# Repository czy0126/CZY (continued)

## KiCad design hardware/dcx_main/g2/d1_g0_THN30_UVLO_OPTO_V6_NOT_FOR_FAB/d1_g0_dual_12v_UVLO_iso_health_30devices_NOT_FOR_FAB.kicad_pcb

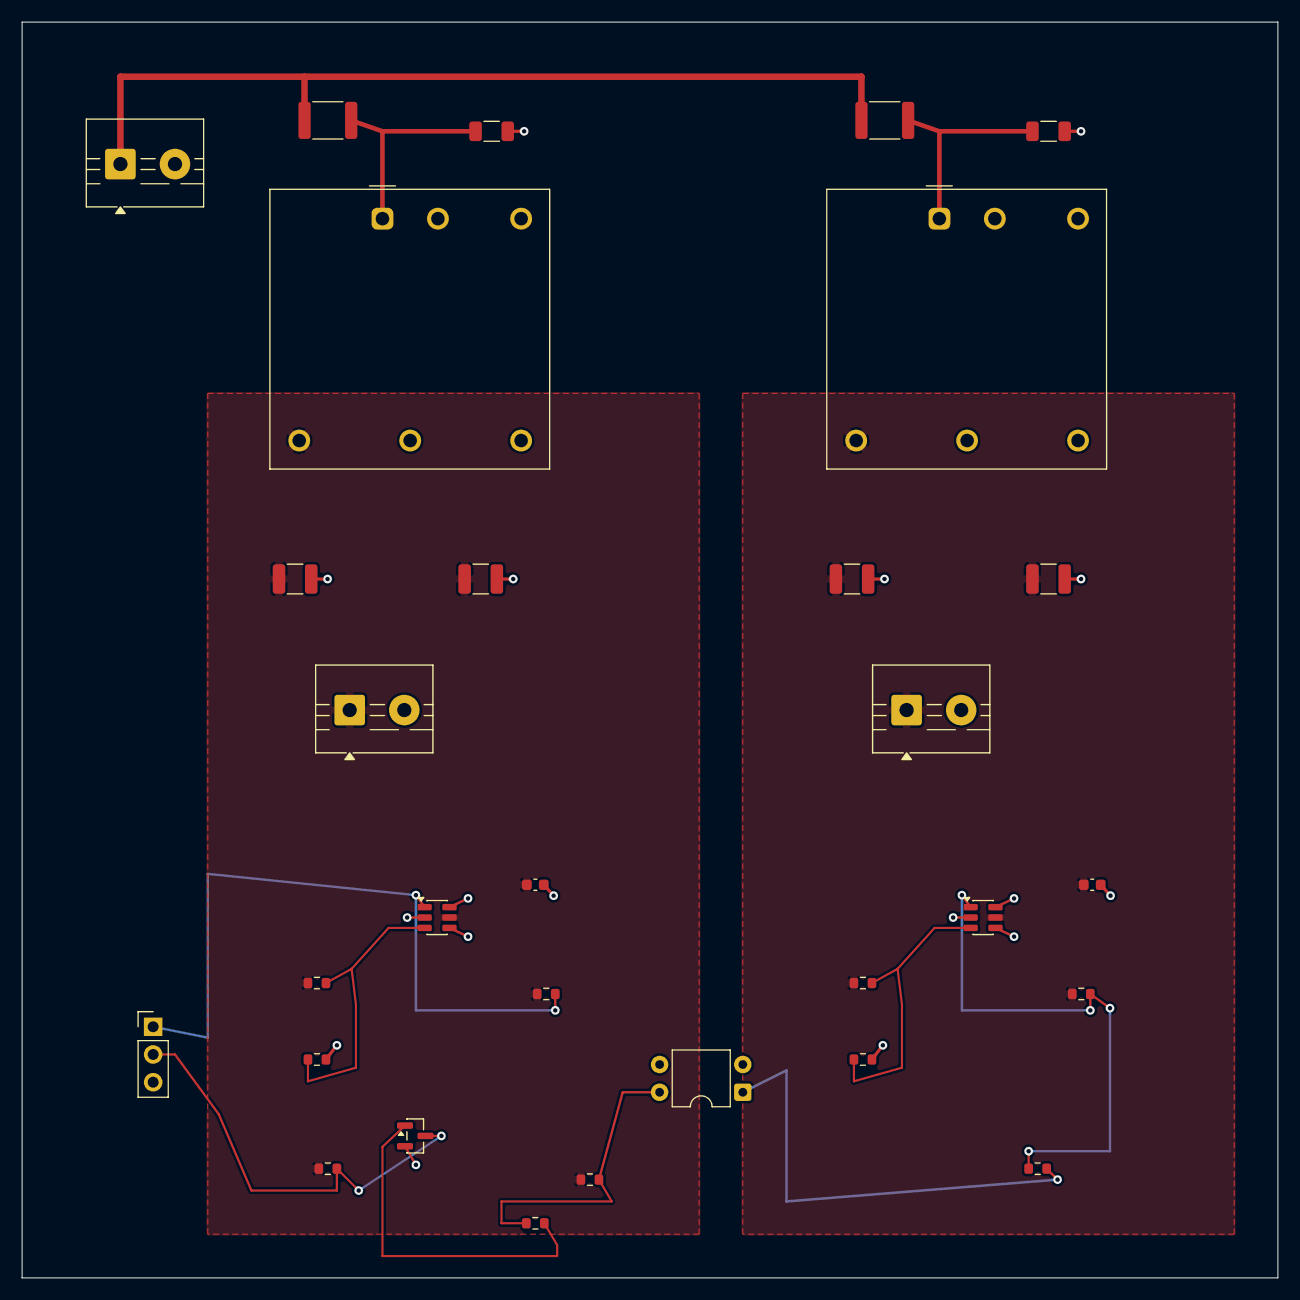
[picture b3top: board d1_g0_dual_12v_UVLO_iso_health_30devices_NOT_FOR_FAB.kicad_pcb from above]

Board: 2 copper layers, 115.0 x 115.0 mm, 30 parts (0 on the bottom side), 15 nets.

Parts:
CP_100N: 100nF_25V_X7R; C_0603_1608Metric
CS_100N: 100nF_25V_X7R; C_0603_1608Metric
C_INP: 1uF_100V_X7R_1206_DERATING_PENDING; C_1206_3216Metric
C_INS: 1uF_100V_X7R_1206_DERATING_PENDING; C_1206_3216Metric
C_P1, C_P2: 22uF_25V_X7R_1210_DERATING_PENDING; C_1210_3225Metric
C_S1, C_S2: 22uF_25V_X7R_1210_DERATING_PENDING; C_1210_3225Metric
F1, F2: 2A_SLOW_75VDC_MIN_Q_DFMR_REQUIRED; Fuse_1812_4532Metric
ISO1: VO617A-3_4PIN_DIP_5.3kVrms_DEVICE_ONLY; DIP-4_W7.62mm
J_HEALTH: PRIMARY_STATUS_ONLY_NO_48V_PERMIT; PinHeader_1x03_P2.54mm_Vertical
J_IN: INPUT_48V_PRE_EST0P; TerminalBlock_MaiXu_MX126-5.0-02P_1x02_P5.00mm
J_P: PRIMARY_12V_OUT; TerminalBlock_MaiXu_MX126-5.0-02P_1x02_P5.00mm
J_S: SECONDARY_12V_OUT; TerminalBlock_MaiXu_MX126-5.0-02P_1x02_P5.00mm
QINV: MMBT3904LT1G; SOT-23
RBASE: 47k_0603; R_0603_1608Metric
RINV: 10k_0603; R_0603_1608Metric
RP_BOT: 10k_1%_0603; R_0603_1608Metric
RP_OPTO: 47k_0603_PHOTO_COLLECTOR; R_0603_1608Metric
RP_PULL: 4.7k_0603; R_0603_1608Metric
RP_TOP: 261k_1%_0603; R_0603_1608Metric
RS_BOT: 10k_1%_0603; R_0603_1608Metric
RS_LED: 100R_0603_OPTO_LED; R_0603_1608Metric
RS_PULL: 2.2k_0603; R_0603_1608Metric
RS_TOP: 261k_1%_0603; R_0603_1608Metric
U1, U2: THN 30-4812; Converter_DCDC_TRACO_THN30-xxxx_THT
UP: TPS3710DDCR_PRIMARY_UVLO; SOT-23-6
US: TPS3710DDCR_SECONDARY_UVLO; SOT-23-6

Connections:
OPT_COL_N: ISO1.4, RBASE.1, RP_OPTO.2
OPT_LED_P: ISO1.1, RS_LED.2
PGND: CP_100N.2, C_INP.2, C_INS.2, C_P1.2, C_P2.2, ISO1.3, J_HEALTH.3, J_IN.2, J_P.2, QINV.2, RP_BOT.2, U1.2, U1.5, U2.2, UP.2, UP.4, UP.6
P_SENSE: RP_BOT.1, RP_TOP.2, UP.3
QBASE: QINV.1, RBASE.2
SR_SOURCE_RETURN: CS_100N.2, C_S1.2, C_S2.2, ISO1.2, J_S.2, RS_BOT.2, U2.5, US.2, US.4, US.6
S_SENSE: RS_BOT.1, RS_TOP.2, US.3
UVLO_P_OK: J_HEALTH.1, RP_PULL.2, UP.1
UVLO_S_OK: RS_LED.1, RS_PULL.2, US.1
UVLO_S_PRIMARY_OK: J_HEALTH.2, QINV.3, RINV.2
VCC12: CP_100N.1, C_P1.1, C_P2.1, J_P.1, RINV.1, RP_OPTO.1, RP_PULL.1, RP_TOP.1, U1.3, UP.5
VCC12_S: CS_100N.1, C_S1.1, C_S2.1, J_S.1, RS_PULL.1, RS_TOP.1, U2.3, US.5
VIN48P_F: C_INP.1, F1.2, U1.1
VIN48S_F: C_INS.1, F2.2, U2.1
VIN48_PRE: F1.1, F2.1, J_IN.1

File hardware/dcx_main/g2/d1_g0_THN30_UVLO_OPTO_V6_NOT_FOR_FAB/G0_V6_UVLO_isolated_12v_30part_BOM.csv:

Reference,Native_KiCad_Footprint,Design_MPN,PinNet,Source,OEM_qualified
CP_100N,Capacitor_SMD:C_0603_1608Metric,100nF_25V_X7R,1=VCC12;2=PGND,TBD,NO
CS_100N,Capacitor_SMD:C_0603_1608Metric,100nF_25V_X7R,1=VCC12_S;2=SR_SOURCE_RETURN,TBD,NO
C_INP,Capacitor_SMD:C_1206_3216Metric,1uF_100V_X7R_1206_DERATING_PENDING,1=VIN48P_F;2=PGND,TBD,NO
C_INS,Capacitor_SMD:C_1206_3216Metric,1uF_100V_X7R_1206_DERATING_PENDING,1=VIN48S_F;2=PGND,TBD,NO
C_P1,Capacitor_SMD:C_1210_3225Metric,22uF_25V_X7R_1210_DERATING_PENDING,1=VCC12;2=PGND,TBD,NO
C_P2,Capacitor_SMD:C_1210_3225Metric,22uF_25V_X7R_1210_DERATING_PENDING,1=VCC12;2=PGND,TBD,NO
C_S1,Capacitor_SMD:C_1210_3225Metric,22uF_25V_X7R_1210_DERATING_PENDING,1=VCC12_S;2=SR_SOURCE_RETURN,TBD,NO
C_S2,Capacitor_SMD:C_1210_3225Metric,22uF_25V_X7R_1210_DERATING_PENDING,1=VCC12_S;2=SR_SOURCE_RETURN,TBD,NO
F1,Fuse:Fuse_1812_4532Metric,2A_SLOW_75VDC_MIN_Q_DFMR_REQUIRED,1=VIN48_PRE;2=VIN48P_F,TBD,NO
F2,Fuse:Fuse_1812_4532Metric,2A_SLOW_75VDC_MIN_Q_DFMR_REQUIRED,1=VIN48_PRE;2=VIN48S_F,TBD,NO
ISO1,Package_DIP:DIP-4_W7.62mm,VO617A-3_4PIN_DIP_5.3kVrms_DEVICE_ONLY,1=OPT_LED_P;2=SR_SOURCE_RETURN;3=PGND;4=OPT_COL_N,Vishay,NO
J_HEALTH,Connector_PinHeader_2.54mm:PinHeader_1x03_P2.54mm_Vertical,PRIMARY_STATUS_ONLY_NO_48V_PERMIT,1=UVLO_P_OK;2=UVLO_S_PRIMARY_OK;3=PGND,TBD,NO
J_IN,TerminalBlock:TerminalBlock_MaiXu_MX126-5.0-02P_1x02_P5.00mm,INPUT_48V_PRE_EST0P,1=VIN48_PRE;2=PGND,TBD,NO
J_P,TerminalBlock:TerminalBlock_MaiXu_MX126-5.0-02P_1x02_P5.00mm,PRIMARY_12V_OUT,1=VCC12;2=PGND,TBD,NO
J_S,TerminalBlock:TerminalBlock_MaiXu_MX126-5.0-02P_1x02_P5.00mm,SECONDARY_12V_OUT,1=VCC12_S;2=SR_SOURCE_RETURN,TBD,NO
QINV,Package_TO_SOT_SMD:SOT-23,MMBT3904LT1G,1=QBASE;2=PGND;3=UVLO_S_PRIMARY_OK,onsemi,NO
RBASE,Resistor_SMD:R_0603_1608Metric,47k_0603,1=OPT_COL_N;2=QBASE,TBD,NO
RINV,Resistor_SMD:R_0603_1608Metric,10k_0603,1=VCC12;2=UVLO_S_PRIMARY_OK,TBD,NO
RP_BOT,Resistor_SMD:R_0603_1608Metric,10k_1%_0603,1=P_SENSE;2=PGND,TBD,NO
RP_OPTO,Resistor_SMD:R_0603_1608Metric,47k_0603_PHOTO_COLLECTOR,1=VCC12;2=OPT_COL_N,TBD,NO
RP_PULL,Resistor_SMD:R_0603_1608Metric,4.7k_0603,1=VCC12;2=UVLO_P_OK,TBD,NO
RP_TOP,Resistor_SMD:R_0603_1608Metric,261k_1%_0603,1=VCC12;2=P_SENSE,TBD,NO
RS_BOT,Resistor_SMD:R_0603_1608Metric,10k_1%_0603,1=S_SENSE;2=SR_SOURCE_RETURN,TBD,NO
RS_LED,Resistor_SMD:R_0603_1608Metric,100R_0603_OPTO_LED,1=UVLO_S_OK;2=OPT_LED_P,TBD,NO
RS_PULL,Resistor_SMD:R_0603_1608Metric,2.2k_0603,1=VCC12_S;2=UVLO_S_OK,TBD,NO
RS_TOP,Resistor_SMD:R_0603_1608Metric,261k_1%_0603,1=VCC12_S;2=S_SENSE,TBD,NO
U1,Converter_DCDC:Converter_DCDC_TRACO_THN30-xxxx_THT,THN 30-4812,1=VIN48P_F;2=PGND;3=VCC12;4=;5=PGND;6=,Traco Power,NO
U2,Converter_DCDC:Converter_DCDC_TRACO_THN30-xxxx_THT,THN 30-4812,1=VIN48S_F;2=PGND;3=VCC12_S;4=;5=SR_SOURCE_RETURN;6=,Traco Power,NO
UP,Package_TO_SOT_SMD:SOT-23-6,TPS3710DDCR_PRIMARY_UVLO,1=UVLO_P_OK;2=PGND;3=P_SENSE;4=PGND;5=VCC12;6=PGND,TI,NO
US,Package_TO_SOT_SMD:SOT-23-6,TPS3710DDCR_SECONDARY_UVLO,1=UVLO_S_OK;2=SR_SOURCE_RETURN;3=S_SENSE;4=SR_SOURCE_RETURN;5=VCC12_S;6=SR_SOURCE_RETURN,TI,NO

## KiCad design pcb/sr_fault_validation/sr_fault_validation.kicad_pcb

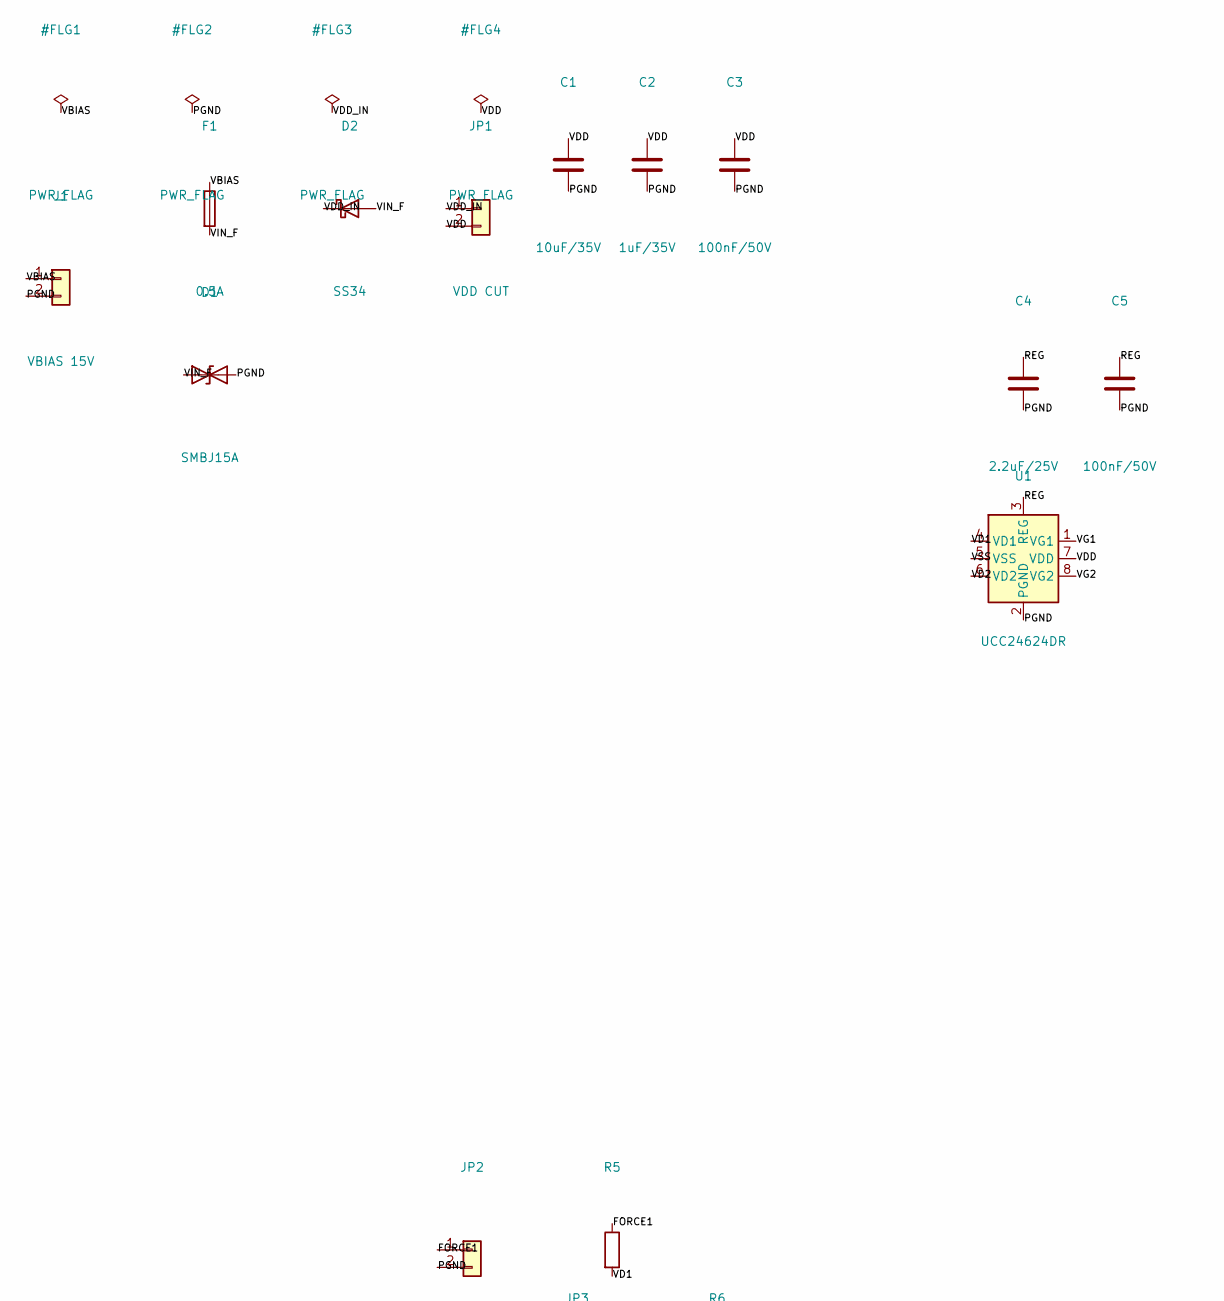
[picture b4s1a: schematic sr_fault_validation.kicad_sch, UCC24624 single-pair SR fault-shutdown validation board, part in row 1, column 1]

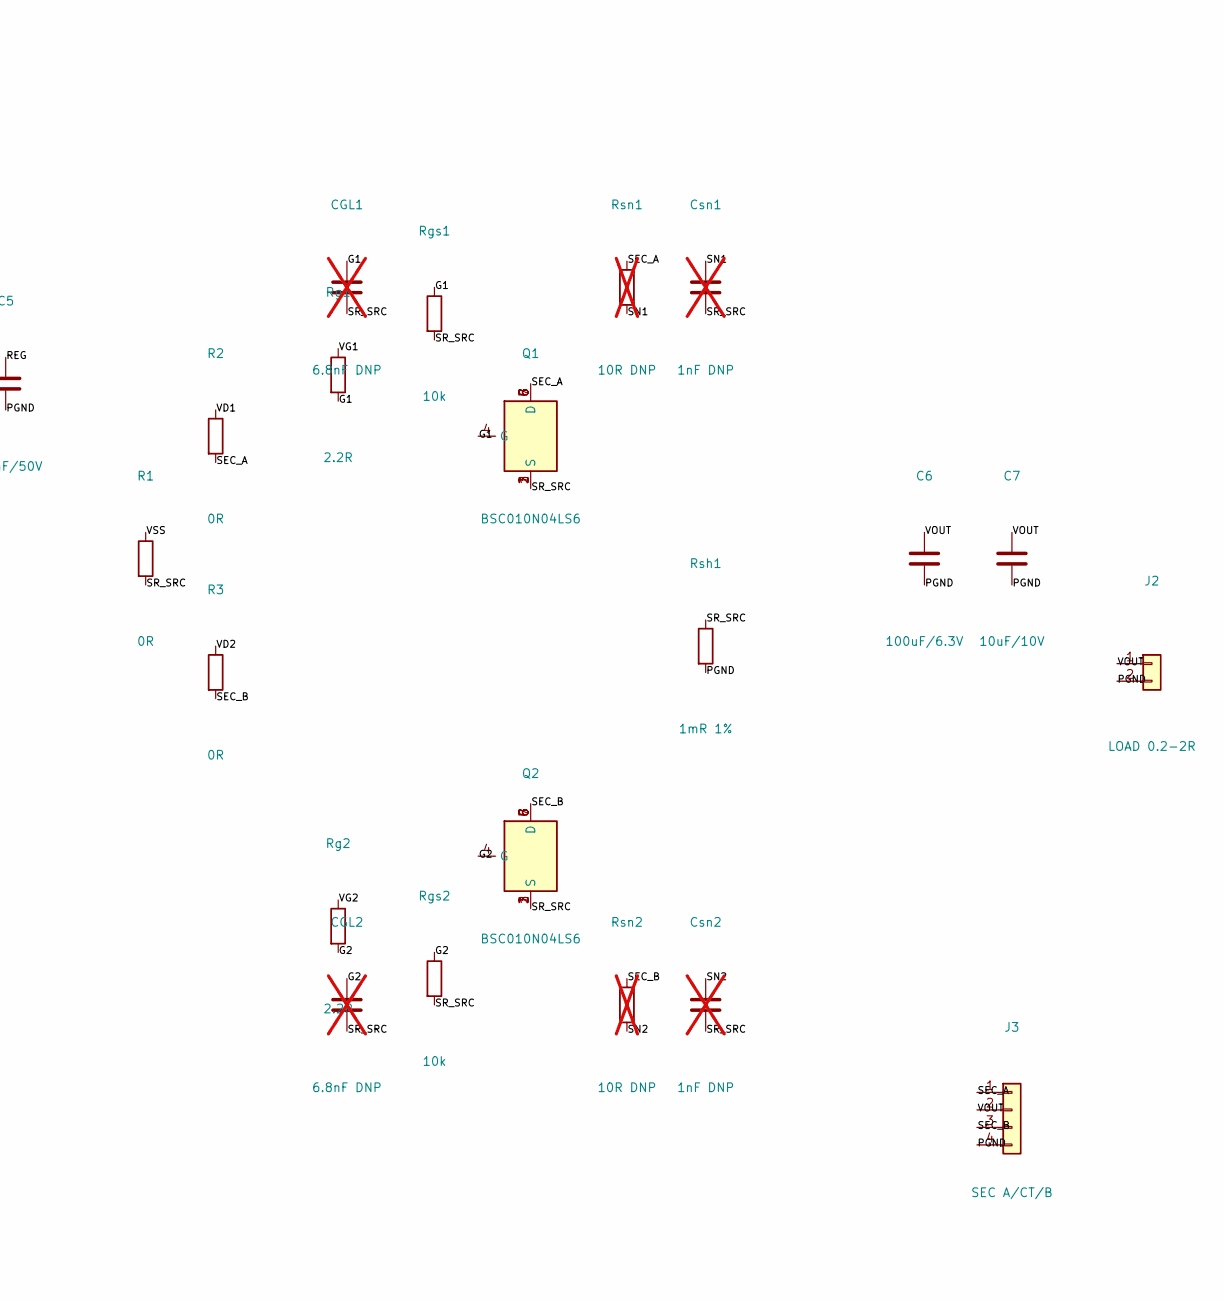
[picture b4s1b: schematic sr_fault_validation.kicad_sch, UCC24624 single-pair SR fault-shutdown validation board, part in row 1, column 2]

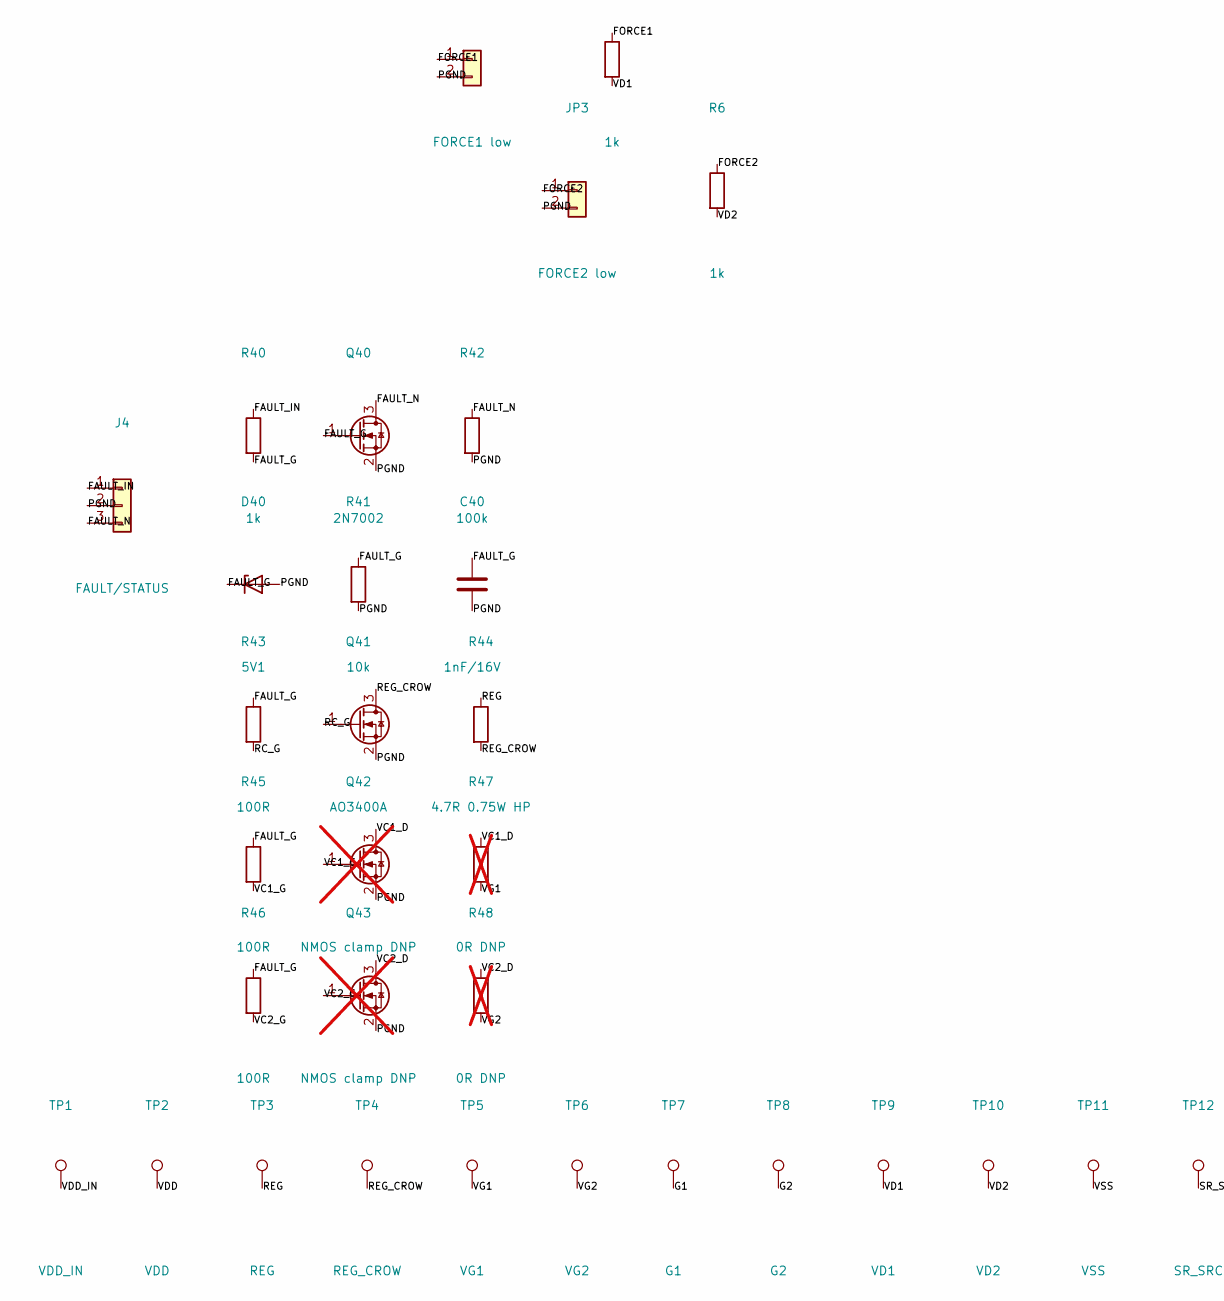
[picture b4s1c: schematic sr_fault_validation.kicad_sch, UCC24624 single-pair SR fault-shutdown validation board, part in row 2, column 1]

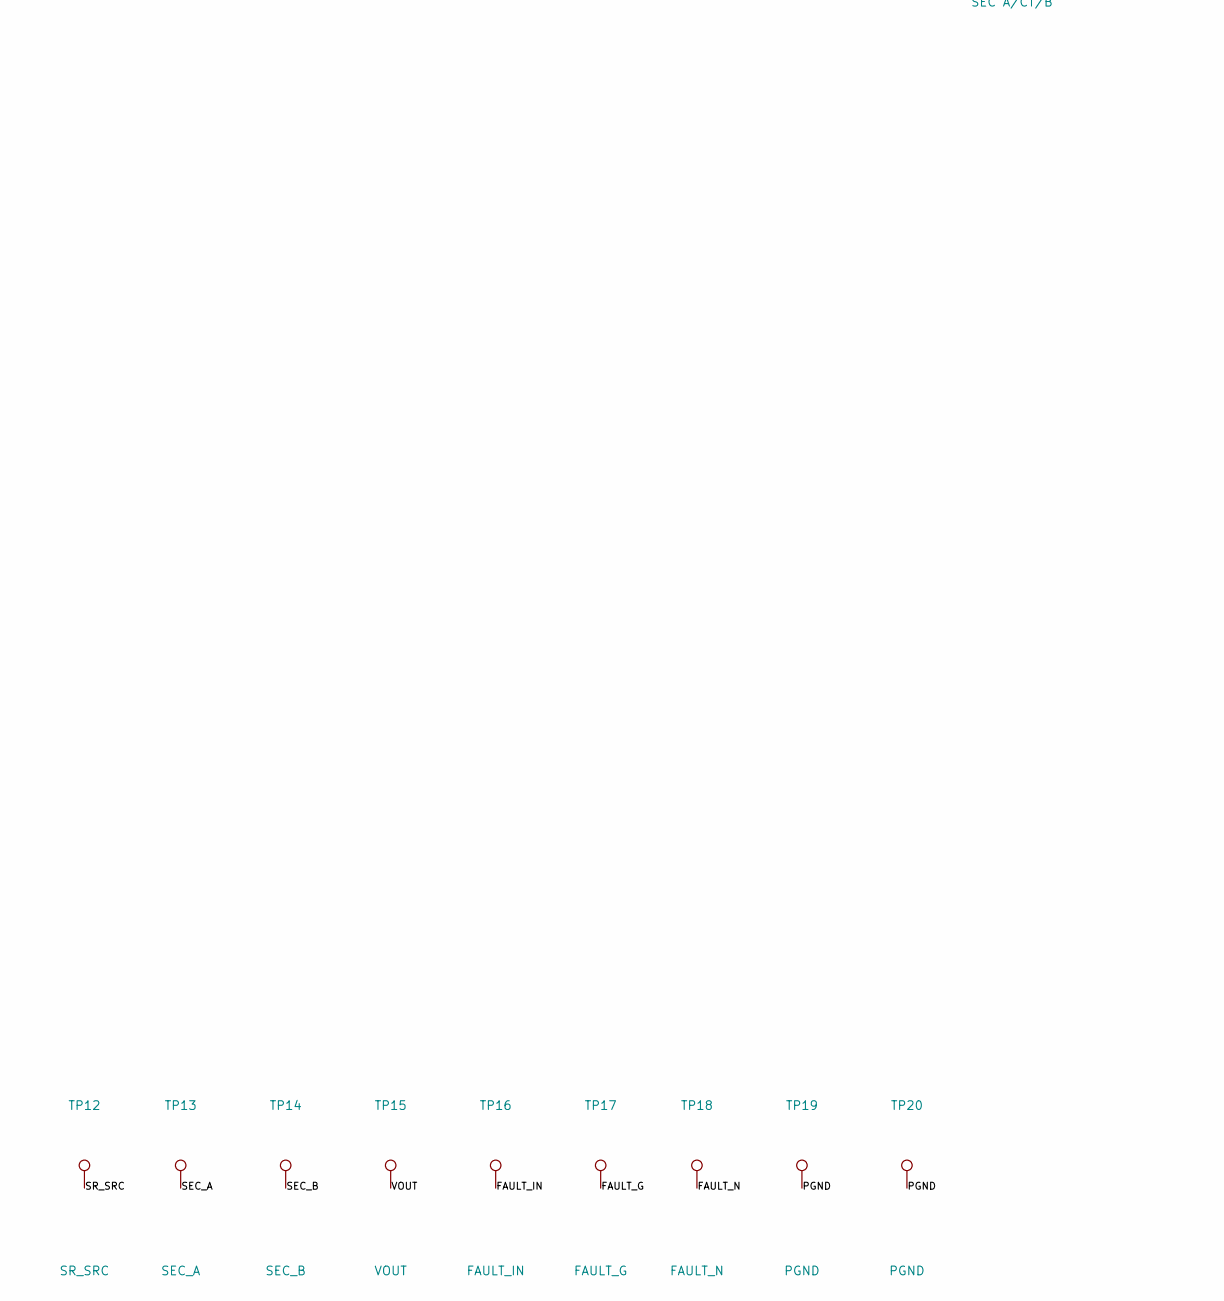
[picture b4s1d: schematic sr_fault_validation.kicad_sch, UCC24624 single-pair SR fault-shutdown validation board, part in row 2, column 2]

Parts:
C1: 10uF/35V; C_1210_3225Metric
C2: 1uF/35V; C_0805_2012Metric
C3, C5: 100nF/50V; C_0603_1608Metric
C4: 2.2uF/25V; C_1206_3216Metric
C6: 100uF/6.3V; C_1210_3225Metric
C7: 10uF/10V; C_0805_2012Metric
C40: 1nF/16V; C_0603_1608Metric
CGL1, CGL2: 6.8nF DNP; C_0603_1608Metric; not fitted
Csn1, Csn2: 1nF DNP; C_0603_1608Metric; not fitted
D1: SMBJ15A; D_SMB
D2: SS34; D_SMA
D40: 5V1; D_SOD-123
F1: 0.5A; Fuse_1206_3216Metric
J1: VBIAS 15V; TerminalBlock_MaiXu_MX126-5.0-02P_1x02_P5.00mm
J2: LOAD 0.2-2R; TerminalBlock_MaiXu_MX126-5.0-02P_1x02_P5.00mm
J3: SEC A/CT/B; TerminalBlock_MaiXu_MX126-5.0-04P_1x04_P5.00mm
J4: FAULT/STATUS; PinHeader_1x03_P2.54mm_Vertical
JP1: VDD CUT; PinHeader_1x02_P2.54mm_Vertical
JP2: FORCE1 low; PinHeader_1x02_P2.54mm_Vertical
JP3: FORCE2 low; PinHeader_1x02_P2.54mm_Vertical
Q1, Q2: BSC010N04LS6
Q40: 2N7002; SOT-23
Q41: AO3400A; SOT-23
Q42, Q43: NMOS clamp DNP; SOT-23; not fitted
R1: 0R; R_0805_2012Metric
R2, R3: 0R; R_0603_1608Metric
R5, R6, R40: 1k; R_0603_1608Metric
R41: 10k; R_0603_1608Metric
R42: 100k; R_0603_1608Metric
R43, R45, R46: 100R; R_0603_1608Metric
R44: 4.7R 0.75W HP; R_1206_3216Metric
R47, R48: 0R DNP; R_0805_2012Metric; not fitted
Rg1, Rg2: 2.2R; R_0805_2012Metric
Rgs1, Rgs2: 10k; R_0603_1608Metric
Rsh1: 1mR 1%; R_2512_6332Metric
Rsn1, Rsn2: 10R DNP; R_0603_1608Metric; not fitted
TP1: VDD_IN; TestPoint_Pad_D1.0mm
TP2: VDD; TestPoint_Pad_D1.0mm
TP3: REG; TestPoint_Pad_D1.0mm
TP4: REG_CROW; TestPoint_Pad_D1.0mm
TP5: VG1; TestPoint_Pad_D1.0mm
TP6: VG2; TestPoint_Pad_D1.0mm
TP7: G1; TestPoint_Pad_D1.0mm
TP8: G2; TestPoint_Pad_D1.0mm
TP9: VD1; TestPoint_Pad_D1.0mm
TP10: VD2; TestPoint_Pad_D1.0mm
TP11: VSS; TestPoint_Pad_D1.0mm
TP12: SR_SRC; TestPoint_Pad_D1.0mm
TP13: SEC_A; TestPoint_Pad_D1.0mm
TP14: SEC_B; TestPoint_Pad_D1.0mm
TP15: VOUT; TestPoint_Pad_D1.0mm
TP16: FAULT_IN; TestPoint_Pad_D1.0mm
TP17: FAULT_G; TestPoint_Pad_D1.0mm
TP18: FAULT_N; TestPoint_Pad_D1.0mm
TP19, TP20: PGND; TestPoint_Pad_D1.0mm
U1: UCC24624DR; SOIC-8_3.9x4.9mm_P1.27mm

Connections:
FAULT_G: C40.1, D40.1 (K), Q40.1 (G), R40.2, R41.1, R43.1, R45.1, R46.1, TP17.1
FAULT_IN: J4.1, R40.1, TP16.1
FAULT_N: J4.3, Q40.3 (D), R42.1, TP18.1
FORCE1: JP2.1, R5.1
FORCE2: JP3.1, R6.1
G1: CGL1.1, Q1.4 (G), Rg1.2, Rgs1.1, TP7.1
G2: CGL2.1, Q2.4 (G), Rg2.2, Rgs2.1, TP8.1
PGND: C1.2, C2.2, C3.2, C4.2, C5.2, C6.2, C7.2, C40.2, D1.2 (A2), D40.2 (A), J1.2, J2.2, J3.4, J4.2, JP2.2, JP3.2, Q40.2 (S), Q41.2 (S), Q42.2 (S), Q43.2 (S), R41.2, R42.2, Rsh1.2, TP19.1, TP20.1, U1.2 (PGND)
RC_G: Q41.1 (G), R43.2
REG: C4.1, C5.1, R44.1, TP3.1, U1.3 (REG)
REG_CROW: Q41.3 (D), R44.2, TP4.1
SEC_A: J3.1, Q1.5 (D), Q1.6 (D), Q1.7 (D), Q1.8 (D), R2.2, Rsn1.1, TP13.1
SEC_B: J3.3, Q2.5 (D), Q2.6 (D), Q2.7 (D), Q2.8 (D), R3.2, Rsn2.1, TP14.1
SN1: Csn1.1, Rsn1.2
SN2: Csn2.1, Rsn2.2
SR_SRC: CGL1.2, CGL2.2, Csn1.2, Csn2.2, Q1.1 (S), Q1.2 (S), Q1.3 (S), Q2.1 (S), Q2.2 (S), Q2.3 (S), R1.2, Rgs1.2, Rgs2.2, Rsh1.1, TP12.1
VBIAS: F1.1, J1.1
VC1_D: Q42.3 (D), R47.1
VC1_G: Q42.1 (G), R45.2
VC2_D: Q43.3 (D), R48.1
VC2_G: Q43.1 (G), R46.2
VD1: R2.1, R5.2, TP9.1, U1.4 (VD1)
VD2: R3.1, R6.2, TP10.1, U1.6 (VD2)
VDD: C1.1, C2.1, C3.1, JP1.2, TP2.1, U1.7 (VDD)
VDD_IN: D2.1 (K), JP1.1, TP1.1
VG1: R47.2, Rg1.1, TP5.1, U1.1 (VG1)
VG2: R48.2, Rg2.1, TP6.1, U1.8 (VG2)
VIN_F: D1.1 (A1), D2.2 (A), F1.2
VOUT: C6.1, C7.1, J2.1, J3.2, TP15.1
VSS: R1.1, TP11.1, U1.5 (VSS)

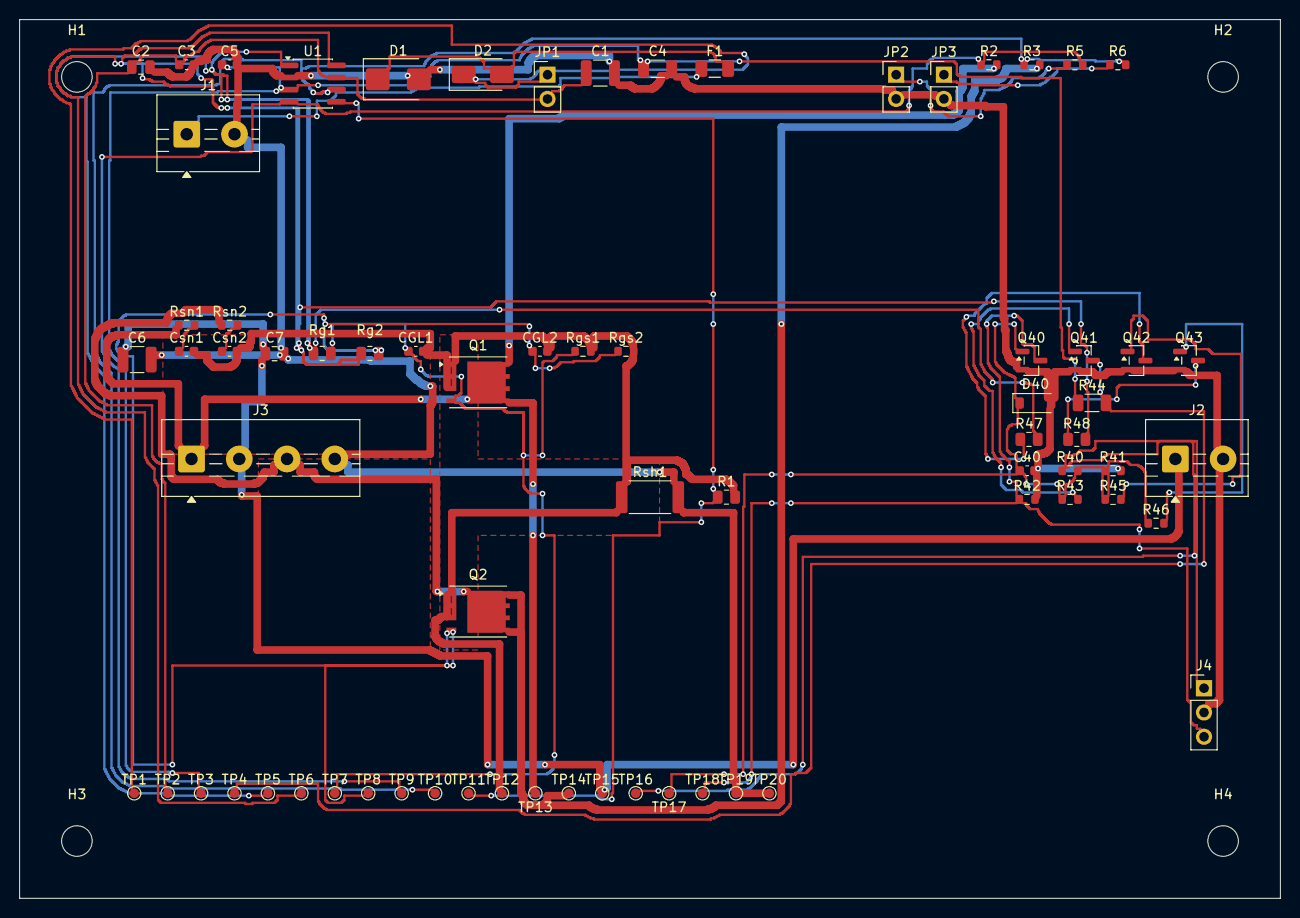
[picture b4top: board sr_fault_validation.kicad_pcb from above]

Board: 2 copper layers, 132.0 x 92.0 mm, 75 parts (0 on the bottom side), 30 nets.

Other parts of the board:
H1, H2, H3, H4: MountingHole_3.2mm_M3

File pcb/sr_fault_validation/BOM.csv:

Reference,Value,Footprint,Rating,Note,DNP,MPN,MPN_Source,LCSC,Qty
J1,VBIAS 15V,TerminalBlock:TerminalBlock_MaiXu_MX126-5.0-02P_1x02_P5.00mm,"15 V, 0.5 A",bias input; polarity marked on the silk,,,TO_SELECT,,1
F1,0.5A,Fuse:Fuse_1206_3216Metric,0.5 A,bias fuse,,,TO_SELECT,,1
D1,SMBJ15A,Diode_SMD:D_SMB,15 V standoff,bias TVS,,,TO_SELECT,,1
D2,SS34,Diode_SMD:D_SMA,40 V 3 A,reverse-polarity block; pin 1 is the cathode,,,TO_SELECT,,1
JP1,VDD CUT,Connector_PinHeader_2.54mm:PinHeader_1x02_P2.54mm_Vertical,,shunt fitted = VDD connected; remove to test a VDD-only cut,,,TO_SELECT,,1
C1,10uF/35V,Capacitor_SMD:C_1210_3225Metric,35 V X7R,,,,TO_SELECT,,1
C2,1uF/35V,Capacitor_SMD:C_0805_2012Metric,35 V X7R,,,,TO_SELECT,,1
C3,100nF/50V,Capacitor_SMD:C_0603_1608Metric,50 V X7R,at pin 7,,,TO_SELECT,,1
U1,UCC24624DR,Package_SO:SOIC-8_3.9x4.9mm_P1.27mm,230 V VD pins,"SR controller, SOIC-8",,UCC24624DR,references/datasheets/ucc24624.txt,,1
C4,2.2uF/25V,Capacitor_SMD:C_1206_3216Metric,25 V X7R,"REG bypass, <=1 cm from pin 3",,,TO_SELECT,,1
C5,100nF/50V,Capacitor_SMD:C_0603_1608Metric,50 V X7R,REG HF bypass,,,TO_SELECT,,1
R1,0R,Resistor_SMD:R_0805_2012Metric,<=212 R option,Roffset: VTHOFF = 10.5 mV + 330 uA * R; 0R keeps the datasheet value,,,TO_SELECT,,1
R2,0R,Resistor_SMD:R_0603_1608Metric,100 R option,VD1 series link; 100R only if drain ringing demands it,,,TO_SELECT,,1
R3,0R,Resistor_SMD:R_0603_1608Metric,100 R option,VD2 series link,,,TO_SELECT,,1
Q1,BSC010N04LS6,dcx:BSC010N04LS6,40 V 1.0 mR,SR1; source Kelvin to VSS,,BSC010N04LS6,references/datasheets/bsc010n04ls6.txt,,1
Q2,BSC010N04LS6,dcx:BSC010N04LS6,40 V 1.0 mR,SR2; source Kelvin to VSS,,BSC010N04LS6,references/datasheets/bsc010n04ls6.txt,,1
Rg1,2.2R,Resistor_SMD:R_0805_2012Metric,1/8 W,"gate resistor, main-board value",,,TO_SELECT,,1
Rg2,2.2R,Resistor_SMD:R_0805_2012Metric,1/8 W,"gate resistor, main-board value",,,TO_SELECT,,1
Rgs1,10k,Resistor_SMD:R_0603_1608Metric,1/10 W,gate-source pulldown,,,TO_SELECT,,1
Rgs2,10k,Resistor_SMD:R_0603_1608Metric,1/10 W,gate-source pulldown,,,TO_SELECT,,1
CGL1,6.8nF DNP,Capacitor_SMD:C_0603_1608Metric,50 V,gate-load test,yes,,TO_SELECT,,1
CGL2,6.8nF DNP,Capacitor_SMD:C_0603_1608Metric,50 V,gate-load test,yes,,TO_SELECT,,1
Rsh1,1mR 1%,Resistor_SMD:R_2512_6332Metric,2 W,return current sense; 10 A -> 10 mV,,,TO_SELECT,,1
Rsn1,10R DNP,Resistor_SMD:R_0603_1608Metric,1/10 W,RC snubber,yes,,TO_SELECT,,1
Csn1,1nF DNP,Capacitor_SMD:C_0603_1608Metric,50 V,RC snubber,yes,,TO_SELECT,,1
Rsn2,10R DNP,Resistor_SMD:R_0603_1608Metric,1/10 W,RC snubber,yes,,TO_SELECT,,1
Csn2,1nF DNP,Capacitor_SMD:C_0603_1608Metric,50 V,RC snubber,yes,,TO_SELECT,,1
J3,SEC A/CT/B,TerminalBlock:TerminalBlock_MaiXu_MX126-5.0-04P_1x04_P5.00mm,"20 V peak, 10 A",isolated low-voltage centre-tapped source,,,TO_SELECT,,1
C6,100uF/6.3V,Capacitor_SMD:C_1210_3225Metric,6.3 V X5R,,,,TO_SELECT,,1
C7,10uF/10V,Capacitor_SMD:C_0805_2012Metric,10 V X7R,,,,TO_SELECT,,1
J2,LOAD 0.2-2R,TerminalBlock:TerminalBlock_MaiXu_MX126-5.0-02P_1x02_P5.00mm,2 A max,load / electronic load,,,TO_SELECT,,1
R5,1k,Resistor_SMD:R_0603_1608Metric,1/10 W,VD1 injection,,,TO_SELECT,,1
R6,1k,Resistor_SMD:R_0603_1608Metric,1/10 W,VD2 injection,,,TO_SELECT,,1
JP2,FORCE1 low,Connector_PinHeader_2.54mm:PinHeader_1x02_P2.54mm_Vertical,,shunt = force VD1 low,,,TO_SELECT,,1
JP3,FORCE2 low,Connector_PinHeader_2.54mm:PinHeader_1x02_P2.54mm_Vertical,,shunt = force VD2 low,,,TO_SELECT,,1
J4,FAULT/STATUS,Connector_PinHeader_2.54mm:PinHeader_1x03_P2.54mm_Vertical,"3.3/5 V CMOS or open-drain, active high","pin 1 = fault request, pin 3 = open-drain status",,,TO_SELECT,,1
R40,1k,Resistor_SMD:R_0603_1608Metric,1/10 W,series limit into the clamp,,,TO_SELECT,,1
D40,5V1,Diode_SMD:D_SOD-123,5.1 V,"input clamp; two-pad land so the cathode (pad 1, the banded end) actually reaches FAULT_G -- an SOT-23 land left pad 3, which is where a BZX84 puts its cathode, as spare copper.  MPN TO_SELECT: no 5.1 V zener datasheet is in the repository",,,TO_SELECT,,1
R41,10k,Resistor_SMD:R_0603_1608Metric,1/10 W,default = no fault (fail-open input); 10k * 1nF = 10 us input filter,,,TO_SELECT,,1
C40,1nF/16V,Capacitor_SMD:C_0603_1608Metric,16 V X7R,10 us; a 1 ms debounce would dominate every other delay,,,TO_SELECT,,1
Q40,2N7002,Package_TO_SOT_SMD:SOT-23,60 V,open-drain status: low while the fault is asserted,,2N7002LT1G,references/datasheets/2n7002lt1g_onsemi_oem_parameters.txt,,1
R42,100k,Resistor_SMD:R_0603_1608Metric,1/10 W,status default low; the external pull-up sees this 100k to PGND,,,TO_SELECT,,1
R43,100R,Resistor_SMD:R_0603_1608Metric,1/10 W,crowbar gate resistor,,,TO_SELECT,,1
Q41,AO3400A,Package_TO_SOT_SMD:SOT-23,"30 V, 5.7 A, IDM 30 A","REG crowbar; 3.0 V gate from a 3.3 V harness, Rds(on) <= 0.048 ohm at 2.5 V VGS (max, 25 C); absorbs 0.001 mJ per event; selected, not qualified (see report q41_selection)",,AO3400A,references/datasheets/ao3400a.txt,,1
R44,4.7R 0.75W HP,Resistor_SMD:R_1206_3216Metric,0.75 W conditional; pulse screen,"sets the discharge tau with Q41; 0.123 mJ / 25.2 W peak per event (4.9 us equivalent), CRCW-HP conditional pulse screen; hardware qualification UNVERIFIED",,CRCW12064R70FKEAHP,references/datasheets/vishay_crcwhpe3_20260317.pdf,,1
R45,100R,Resistor_SMD:R_0603_1608Metric,1/10 W,VG1 clamp gate resistor,,,TO_SELECT,,1
Q42,NMOS clamp DNP,Package_TO_SOT_SMD:SOT-23,30 V,optional VG1 clamp; contention test only,yes,,TO_SELECT,,1
R47,0R DNP,Resistor_SMD:R_0805_2012Metric,1/4 W,clamp link: fitting this removes U1's ability to hold VG1 high,yes,,TO_SELECT,,1
R46,100R,Resistor_SMD:R_0603_1608Metric,1/10 W,VG2 clamp gate resistor,,,TO_SELECT,,1
Q43,NMOS clamp DNP,Package_TO_SOT_SMD:SOT-23,30 V,optional VG2 clamp; contention test only,yes,,TO_SELECT,,1
R48,0R DNP,Resistor_SMD:R_0805_2012Metric,1/4 W,clamp link,yes,,TO_SELECT,,1
TP1,VDD_IN,TestPoint:TestPoint_Pad_D1.0mm,1 mm pad,scope probe / Kelvin point,,,TO_SELECT,,1
TP2,VDD,TestPoint:TestPoint_Pad_D1.0mm,1 mm pad,scope probe / Kelvin point,,,TO_SELECT,,1
TP3,REG,TestPoint:TestPoint_Pad_D1.0mm,1 mm pad,scope probe / Kelvin point,,,TO_SELECT,,1
TP4,REG_CROW,TestPoint:TestPoint_Pad_D1.0mm,1 mm pad,scope probe / Kelvin point,,,TO_SELECT,,1
TP5,VG1,TestPoint:TestPoint_Pad_D1.0mm,1 mm pad,scope probe / Kelvin point,,,TO_SELECT,,1
TP6,VG2,TestPoint:TestPoint_Pad_D1.0mm,1 mm pad,scope probe / Kelvin point,,,TO_SELECT,,1
TP7,G1,TestPoint:TestPoint_Pad_D1.0mm,1 mm pad,scope probe / Kelvin point,,,TO_SELECT,,1
TP8,G2,TestPoint:TestPoint_Pad_D1.0mm,1 mm pad,scope probe / Kelvin point,,,TO_SELECT,,1
TP9,VD1,TestPoint:TestPoint_Pad_D1.0mm,1 mm pad,scope probe / Kelvin point,,,TO_SELECT,,1
TP10,VD2,TestPoint:TestPoint_Pad_D1.0mm,1 mm pad,scope probe / Kelvin point,,,TO_SELECT,,1
TP11,VSS,TestPoint:TestPoint_Pad_D1.0mm,1 mm pad,scope probe / Kelvin point,,,TO_SELECT,,1
TP12,SR_SRC,TestPoint:TestPoint_Pad_D1.0mm,1 mm pad,scope probe / Kelvin point,,,TO_SELECT,,1
TP13,SEC_A,TestPoint:TestPoint_Pad_D1.0mm,1 mm pad,scope probe / Kelvin point,,,TO_SELECT,,1
TP14,SEC_B,TestPoint:TestPoint_Pad_D1.0mm,1 mm pad,scope probe / Kelvin point,,,TO_SELECT,,1
TP15,VOUT,TestPoint:TestPoint_Pad_D1.0mm,1 mm pad,scope probe / Kelvin point,,,TO_SELECT,,1
TP16,FAULT_IN,TestPoint:TestPoint_Pad_D1.0mm,1 mm pad,scope probe / Kelvin point,,,TO_SELECT,,1
TP17,FAULT_G,TestPoint:TestPoint_Pad_D1.0mm,1 mm pad,scope probe / Kelvin point,,,TO_SELECT,,1
TP18,FAULT_N,TestPoint:TestPoint_Pad_D1.0mm,1 mm pad,scope probe / Kelvin point,,,TO_SELECT,,1
TP19,PGND,TestPoint:TestPoint_Pad_D1.0mm,1 mm pad,scope probe / Kelvin point,,,TO_SELECT,,1
TP20,PGND,TestPoint:TestPoint_Pad_D1.0mm,1 mm pad,scope probe / Kelvin point,,,TO_SELECT,,1

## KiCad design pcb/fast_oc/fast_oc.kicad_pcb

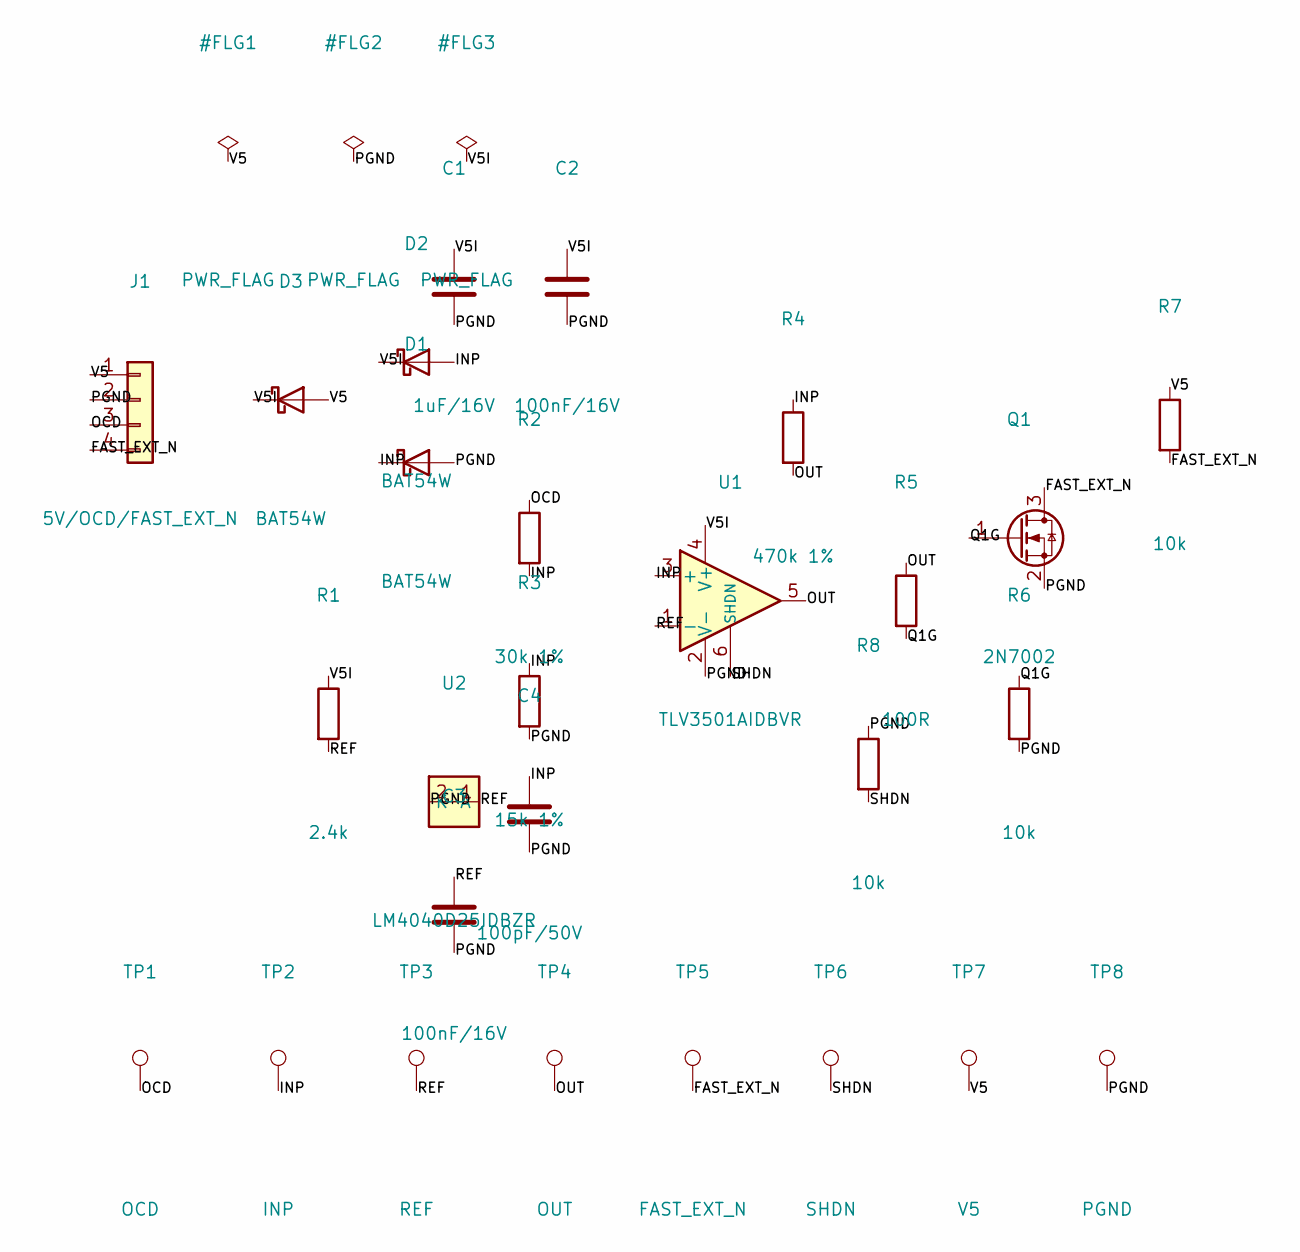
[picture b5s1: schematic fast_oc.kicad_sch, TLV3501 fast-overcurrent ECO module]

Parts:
C1: 1uF/16V; C_0603_1608Metric
C2, C3: 100nF/16V; C_0603_1608Metric
C4: 100pF/50V; C_0603_1608Metric
D1, D2, D3: BAT54W; D_SOD-123
J1: 5V/OCD/FAST_EXT_N; PinHeader_1x04_P2.54mm_Vertical
Q1: 2N7002; SOT-23
R1: 2.4k; R_0603_1608Metric
R2: 30k 1%; R_0603_1608Metric
R3: 15k 1%; R_0603_1608Metric
R4: 470k 1%; R_0603_1608Metric
R5: 100R; R_0603_1608Metric
R6, R7, R8: 10k; R_0603_1608Metric
TP1: OCD; TestPoint_Pad_D1.0mm
TP2: INP; TestPoint_Pad_D1.0mm
TP3: REF; TestPoint_Pad_D1.0mm
TP4: OUT; TestPoint_Pad_D1.0mm
TP5: FAST_EXT_N; TestPoint_Pad_D1.0mm
TP6: SHDN; TestPoint_Pad_D1.0mm
TP7: V5; TestPoint_Pad_D1.0mm
TP8: PGND; TestPoint_Pad_D1.0mm
U1: TLV3501AIDBVR; SOT-23-6
U2: LM4040D25IDBZR; SOT-23

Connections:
FAST_EXT_N: J1.4, Q1.3 (D), R7.2, TP5.1
INP: C4.1, D1.1 (K), D2.2 (A), R2.2, R3.1, R4.1, TP2.1, U1.3 (+)
OCD: J1.3, R2.1, TP1.1
OUT: R4.2, R5.1, TP4.1, U1.5
PGND: C1.2, C2.2, C3.2, C4.2, D1.2 (A), J1.2, Q1.2 (S), R3.2, R6.2, R8.1, TP8.1, U1.2 (V-), U2.2 (A)
Q1G: Q1.1 (G), R5.2, R6.1
REF: C3.1, R1.2, TP3.1, U1.1 (-), U2.1 (K)
SHDN: R8.2, TP6.1, U1.6 (SHDN)
V5: D3.2 (A), J1.1, R7.1, TP7.1
V5I: C1.1, C2.1, D2.1 (K), D3.1 (K), R1.1, U1.4 (V+)

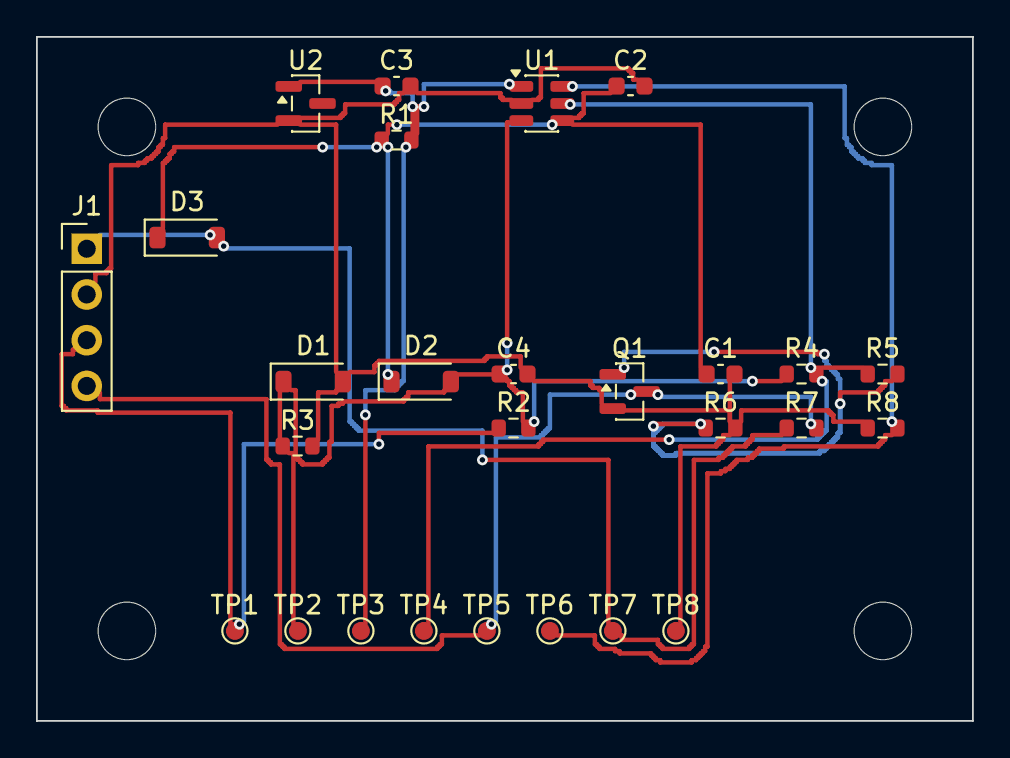
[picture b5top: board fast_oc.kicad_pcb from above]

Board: 2 copper layers, 52.0 x 38.0 mm, 31 parts (0 on the bottom side), 10 nets.

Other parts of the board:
H1, H2, H3, H4: MountingHole_3.2mm_M3
